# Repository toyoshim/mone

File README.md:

# MONE - Mini console Oriented NEOGEO converter

## Overview

This is a small box for you to use NEOGEO gamepad on playing multiple mini consoles.
Currently it supports

- NEOGEO mini
- MEGADRIVE mini
- PC-Engine mini
- Playstation Classic
- Retro-bit Generations IV (and maybe other variants)
- THE C64 MINI

Also it supports features to configure button layout, and assign rapid fire mode for arbitrary buttons.

## Features

### Multiple console supports

MONE is recognized as a USB HID device, and it's device information will change based on DIPSW.
If you change DIPSW, the device will reconnect and the host will recognize the new console mode.

Here is the list for DIPSW.

- 000x: NEOGEO mini
- 100x: MEGADRIVE mini
- 010x: PC-Engine mini
- 110x: Playstation Classic
- 001x: Retro-bit Generations
- 101x: THE C64 MINI
- 011x: (reserved)
- 111x: (reserved)

DIPSW 4 is not used to choose a mini console mode, but you can save layout and rapid fire settings for each.
So, you can have 2 different settings for each console.

### Button Layout

Once you push the button on the PCB, MONE goes into a button layout configuration mode. You can choose arbitray physical button sets for logical button 1, 2, 3, 4, 5, 6, 7, and 8. You can choose multiple physical buttons for one logical button, and can assign one of them as a rapid fire mode, e.g. choosing physical button 1 and 3 for the logical button 1, and button 3 can be a rapid fire button for the 1.

By default, MONE assumes that the physical button layout is something like this:

```
       2     3
  1
      5    6
4
```

And each console mode maps these physical buttons into their own buttons.
Here is the matrix.

| Mode \ Button         | COIN |START| 1 | 2 | 3 | 4 | 5 | 6 | 7 | 8 |
|-----------------------|------|-----|---|---|---|---|---|---|---|---|
| NEOGEO mini           |SELECT|START| B | C | D | A | - | - | - | - |
| MEGADRIVE mini        | HOME |START| A | B | C | X | Y | Z | - | - |
| PC-Engine mini        |SELECT| RUN |II | I | - | - | - | - | - | - |
| Playstation Classic   |SELECT|START| □ | × | ○ | △ |L2 |R2 |L1 |R1 |
| Retro-bit Generations | MODE |START| 1 | 2 | 3 | 4 | 5 | 6 | - | - |
| THE C64 MINI          |  C   |MENU |LF |RF |TL |TR | A | B | - | - |

You can change the layout for each mode as follows.

Steps:

1. Puth the button on the PCB
2. Push gamepad buttons for the logical coin (e.g. B on NEOGEO mini), and release them
3. Push gamepad buttons for the logical start (e.g. C on NEOGEO mini), and release them
4. Push gamepad buttons for the logical button 1 (e.g. C on NEOGEO mini), and release them
4. Continue for 2, 3, ..., and 8
5. Push the button on the PCB to configure rapid fire buttons

You can quit the layout configuration mode anytime by pushing the button on the PCB.
If you skip all, layout won't be changed, but if you set some buttons partially, remaining buttons are assigned to no button.

### Rapid Fire

After setting the layout mode, you can enter the rapid fire configuration mode.
Push buttons those you want to make it rapid fire buttons, then push the button on the PCB again.
You can got to the rapid fire speed setting mode.

For instance, you can assign physical buttons 1 and 3 to logical button B in the layout mode, and can assign button 3 as a rapid fire button B here. Thus, you can use gamepad button 1 for a normal button B, and use button 3 for a rapid fire button B.

Once you quit the rapid fire configuration mode, now you can choose the rapid fire speed.
Push one of following button to select the speed. Note that the number is for specifying the button in the original physical layout. You can quit the speed setting mode by pushing the button on the PCB. Now you can get back to the normal operation.

| Button |  1 |  2 |  3 |  4 |
|--------|----|----|----|----|
| Speed  | 12 | 15 | 20 | 30 |

### Settings

When you finish the layout and rapid fire settings, all configurations are stored into the flash ROM.
You can save the settings per each DIPSW mode, that means you can keep 2 settings for each console mode.

### 6 Buttons

The original NEOGEO has only 4 buttons, but there are unused pins. MONE uses these unused pins for button 5 and 6.
This is the same with some Japanese arcade control boxes. See the schematics below to check details.

Also, complete KiCad data is available in the repository so to order your own PCB.

## Schematics

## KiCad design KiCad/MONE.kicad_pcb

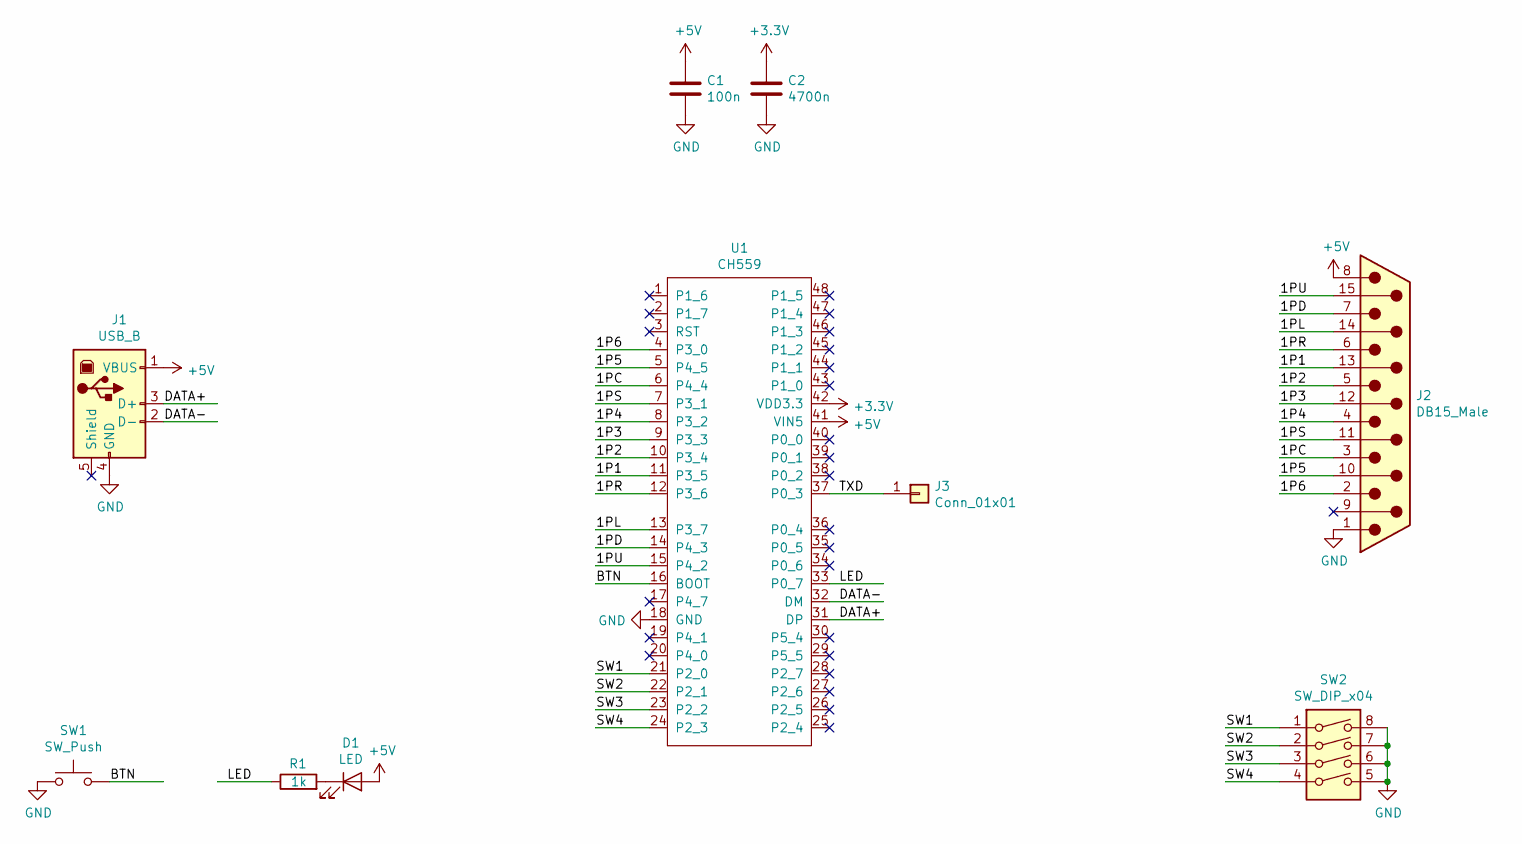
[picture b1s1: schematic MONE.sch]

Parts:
C1: 100n; C_0603_1608Metric_Pad1.05x0.95mm_HandSolder
C2: 4700n; C_0603_1608Metric_Pad1.05x0.95mm_HandSolder
D1: LED; LED_D3.0mm
J1: USB_B; USB_B_OST_USB-B1HSxx_Horizontal
J2: DB15_Male; DSUB-15_Male_Horizontal_P2.77x2.84mm_EdgePinOffset4.94mm_Ho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
J3: Conn_01x01; PinHeader_1x01_P2.54mm_Vertical
R1: 1k; R_0603_1608Metric_Pad1.05x0.95mm_HandSolder
SW1: SW_Push; SW_PUSH_6mm_H4.3mm
SW2: SW_DIP_x04; SW_DIP_SPSTx04_Slide_9.78x12.34mm_W7.62mm_P2.54mm
U1: CH559; LQFP-48_7x7mm_P0.5mm

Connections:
+3V3: C2.1, U1.42 (VDD3.3)
+5V: C1.1, D1.2 (A), J1.1 (VBUS), J2.8, U1.41 (VIN5)
/1P1: J2.13, U1.11 (P3_5)
/1P2: J2.5, U1.10 (P3_4)
/1P3: J2.12, U1.9 (P3_3)
/1P4: J2.4, U1.8 (P3_2)
/1P5: J2.10, U1.5 (P4_5)
/1P6: J2.2, U1.4 (P3_0)
/1PC: J2.3, U1.6 (P4_4)
/1PD: J2.7, U1.14 (P4_3)
/1PL: J2.14, U1.13 (P3_7)
/1PR: J2.6, U1.12 (P3_6)
/1PS: J2.11 (P111), U1.7 (P3_1)
/1PU: J2.15, U1.15 (P4_2)
/BTN: SW1.2, U1.16 (BOOT)
/DATA+: J1.3 (D+), U1.31 (DP)
/DATA-: J1.2 (D-), U1.32 (DM)
/LED: R1.1, U1.33 (P0_7)
/SW1: SW2.1, U1.21 (P2_0)
/SW2: SW2.2, U1.22 (P2_1)
/SW3: SW2.3, U1.23 (P2_2)
/SW4: SW2.4, U1.24 (P2_3)
/TXD: J3.1, U1.37 (P0_3)
GND: C1.2, C2.2, J1.4 (GND), J2.1, SW1.1, SW2.5, SW2.6, SW2.7, SW2.8, U1.18 (GND)
unnamed: D1.1 (K), R1.2

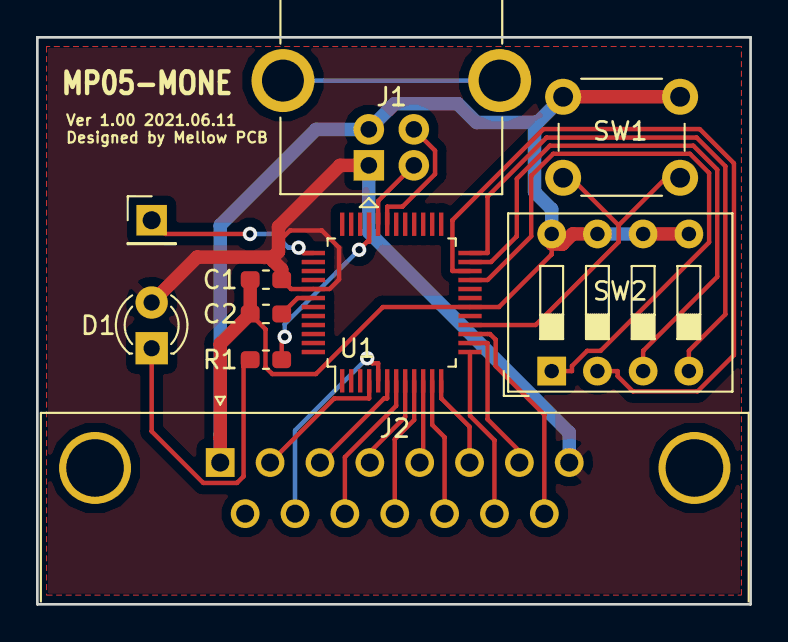
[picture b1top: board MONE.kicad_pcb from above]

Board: 2 copper layers, 39.6 x 31.5 mm, 10 parts (0 on the bottom side), 25 nets.

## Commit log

2021-06-19 initial commit: add chlib submodule and LICENSE
2021-06-19 Add CH55x_python_flasher
2021-06-19 minimum implementation to support NEOGEO mini
2021-06-19 split descriptors
2021-06-19 support multiple descriptor mode
2021-06-19 Add MD mini support
2021-06-19 Add PC-Engine mini support
2021-06-19 Add PS classic support
2021-06-20 add dipsw and button handling
2021-06-20 implement led service
2021-06-22 chlib roll
2021-06-22 NEOGEO mini is now confirmed to work
2021-06-22 Confirmed to support MD mini and Astro mini
2021-06-23 confirm that pc-engine mini works
2021-06-23 support playstation classic
2021-06-23 retro-bit generations
2021-06-26 move led.* to chlib
2021-06-27 Add settings.[c|h]
2021-06-27 move dipsw handling to settings.[c|h]
2021-06-27 move controller handling to controller.[c|h]
2021-06-27 move descriptor related handling to descriptors.[c|h]
2021-06-27 clean up
2021-06-27 move button related enums to settings.h
2021-06-27 prepare to implement settings UI
2021-06-27 implement settings UI
2021-06-27 implement rapid fire
2021-06-27 remove debug code
2021-06-28 settings: do not reset layout if completely skipped
2021-06-30 build with -D_NO_UART0
2021-06-30 Add KiCad data
2021-06-30 make it work safely with unsupported DIPSW modes
2021-06-30 Add README.md
2021-07-17 setting bug fix
2021-07-17 THE C64 MINI support
